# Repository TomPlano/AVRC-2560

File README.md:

# AVRC-2560
Project for interfacing Atmega2560 to the rcbus

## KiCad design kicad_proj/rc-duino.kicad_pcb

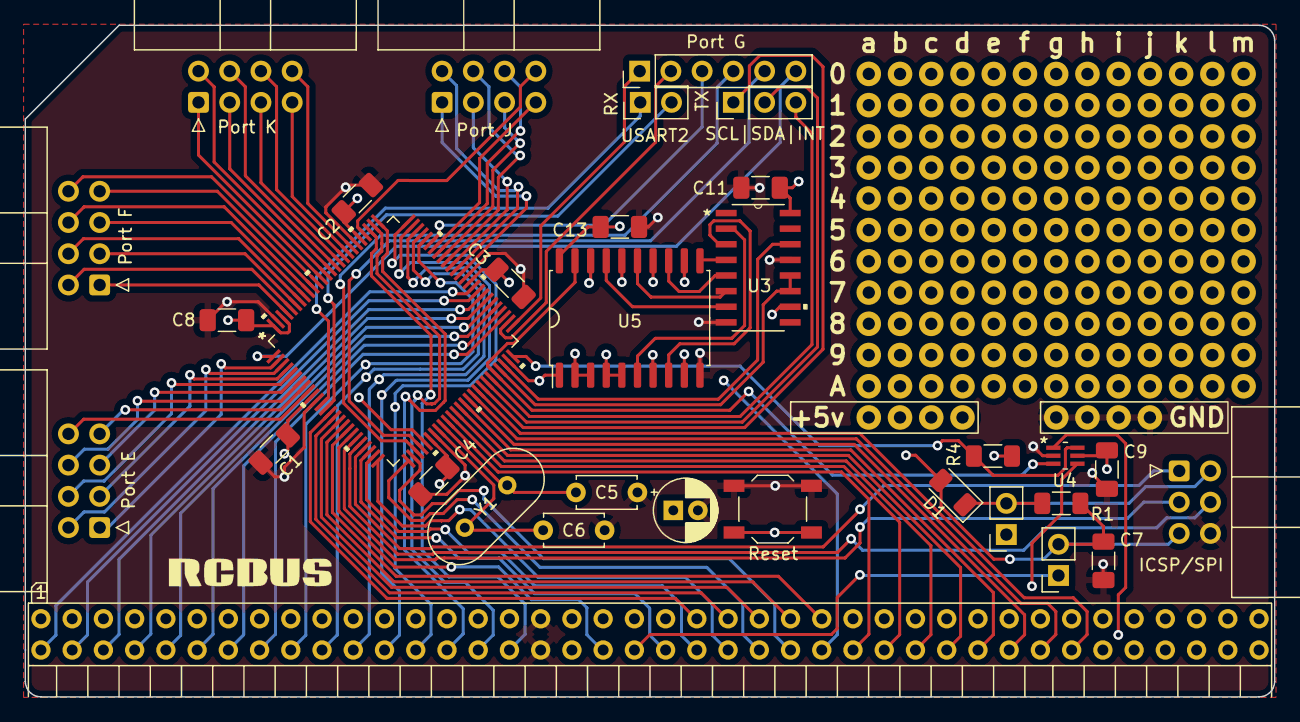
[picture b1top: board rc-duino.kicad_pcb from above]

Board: 4 copper layers, 101.6 x 54.6 mm, 35 parts (1 on the bottom side), 99 nets.

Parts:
47uf1: C_Polarized; CP_Radial_D5.0mm_P2.00mm
C1, C2, C3, C4, C8, C9, C11, C13: .1uf; C_1206_3216Metric_Pad1.33x1.80mm_HandSolder
C5, C6: 20pF; C_Disc_D4.7mm_W2.5mm_P5.00mm
C7: .1uF; C_1206_3216Metric_Pad1.33x1.80mm_HandSolder
D1: D; D_1206_3216Metric
H1: AVRC-Logo; avrc_2560
H2: RCBus Logo; RCBUS
J1: Conn_01x03_Male; PinHeader_1x03_P2.54mm_Vertical
J2: Conn_01x06_Male; PinHeader_1x06_P2.54mm_Vertical
J3: Conn_01x02_Male; PinHeader_1x02_P2.54mm_Vertical
J4, J5, J6: Conn_01x08_Male; IDC-Header_2x04_P2.54mm_Horizontal
J7: proto_area_power_gnd; protoarea
J8: Conn_02x03_Odd_Even; IDC-Header_2x03_P2.54mm_Horizontal
J10: Conn_01x04_Male; IDC-Header_2x04_P2.54mm_Horizontal
J13, J14: Conn_01x02_Male; PinSocket_1x02_P2.54mm_Vertical
R1: 10K; R_1206_3216Metric_Pad1.30x1.75mm_HandSolder
R4: 10k; R_1206_3216Metric_Pad1.30x1.75mm_HandSolder
Reset: SW_Push; SW_SPST_TL3342
U1: RCBus
U2: ATMEGA2560-16AUR
U3: 74HCT595D
U4: SN74LVC1G374DCKR
U5: 74HCT688; SOIC-20W_7.5x12.8mm_P1.27mm
Y1: 16Mhz Crystal; Crystal_HC49-U_Vertical

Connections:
/SCL: J1.1, U2.43 (PD0SCL/INT0)
/SDA: J1.2, U2.44 (PD1SDA/INT1)
/i2c int: J1.3, U2.45 (PD2RXD1/INT2)
/pe0: J6.1, U2.2 (PE0RXD0/PCINT8)
/pe1: J6.2, U2.3 (PE1TXD0)
/pe2: J6.3, U2.4 (PE2XCK0/AIN0)
/pe3: J6.4, U2.5 (PE3OC3A/AIN0)
/pe4: J6.5, U2.6 (PE4OC3B/INT4)
/pe5: J6.6, U2.7 (PE5OC3C/INT5)
/pe6: J6.7, U2.8 (PE6T3/INT6)
/pe7: J6.8, U2.9 (PE7CLKO/ICP3/INT7)
/pf0: J10.1, U2.97 (PF0ADC0)
/pf1: J10.2, U2.96 (PF1ADC1)
/pf2: J10.3, U2.95 (PF2ADC2)
/pf3: J10.4, U2.94 (PF3ADC3)
/pf4: J10.5, U2.93 (PF4ADC4/TCK)
/pf5: J10.6, U2.92 (PF5ADC5/TMS)
/pf6: J10.7, U2.91 (PF6ADC6/TDO)
/pf7: J10.8, U2.90 (PF7ADC7/TDI)
/pg0: J2.1, U2.51 (PG0*WR)
/pg1: J2.2, U2.52 (PG1*RD)
/pg2: J2.3, U2.70 (PG2ALE)
/pg3: J2.4, U2.28 (PG3TOSC2)
/pg4: J2.5, U2.29 (PG4TOSC1)
/pg5: J2.6, U2.1 (PG5OC0B)
/pj0: J4.1, U2.63 (PJ0RXD3/PCINT9)
/pj1: J4.2, U2.64 (PJ1TXD3/PCINT10)
/pj2: J4.3, U2.65 (PJ2XCK3/PCINT11)
/pj3: J4.4, U2.66 (PJ3PCINT12)
/pj4: J4.5, U2.67 (PJ4PCINT13)
/pj5: J4.6, U2.68 (PJ5PCINT14)
/pj6: J4.7, U2.69 (PJ6PCINT15)
/pj7: J4.8, U2.79 (PJ7)
/pk0: J5.1, U2.89 (PK0ADC8/PCINT16)
/pk1: J5.2, U2.88 (PK1ADC9/PCINT17)
/pk2: J5.3, U2.87 (PK2ADC10/PCINT18)
/pk3: J5.4, U2.86 (PK3ADC11/PCINT19)
/pk4: J5.5, U2.85 (PK4ADC12/PCINT20)
/pk5: J5.6, U2.84 (PK5ADC13/PCINT21)
/pk6: J5.7, U2.83 (PK6ADC14/PCINT22)
/pk7: J5.8, U2.82 (PK7ADC15/PCINT23)
/uart2_rx: J3.1, U2.12 (PH0RXD2)
/uart2_tx: J3.2, U2.13 (PH1TXD2)
A0: U1.16 (A0), U2.78 (PA0AD0), U5.2 (P0), U5.3 (R0)
A1: U1.15 (A1), U2.77 (PA1AD1), U5.4 (P1), U5.5 (R1)
A2: U1.14 (A2), U2.76 (PA2AD2), U5.7 (R2)
A3: U1.13 (A3), U2.75 (PA3AD3), U5.9 (R3)
A4: U1.12 (A4), U2.74 (PA4AD4), U5.12 (R4)
A5: U1.11 (A5), U2.73 (PA5AD5), U5.14 (R5)
A6: U1.10 (A6), U2.72 (PA6AD6), U5.16 (R6)
A7: U1.9 (A7), U2.71 (PA7AD7), U5.18 (R7)
A8: U1.8 (A8), U2.53 (PC0A8)
A9: U1.7 (A9), U2.54 (PC1A9)
Aa: U1.6 (A10), U2.55 (PC2A10)
Ab: U1.5 (A11), U2.56 (PC3A11)
Ac: U1.4 (A12), U2.57 (PC4A12)
Ad: U1.3 (A13), U2.58 (PC5A13)
Ae: U1.2 (A14), U2.59 (PC6A14)
Af: U1.1 (A15), U2.60 (PC7A15)
BusAck: U1.62 (~BUSACK), U2.14 (PH2XCK2)
BusRQ: U1.64 (~BUSRQ), U2.16 (PH4OC4B)
CLK: U1.21 (CLOCK), U2.23 (PB4OC2A/PCINT4), U4.1 (CLK)
D0: U1.27 (D0), U2.35 (PL0ICP4)
D1: U1.28 (D1), U2.36 (PL1ICP5)
D2: U1.29 (D2), U2.37 (PL2T5)
D3: U1.30 (D3), U2.38 (PL3OC5A)
D4: U1.31 (D4), U2.39 (PL4OC5B)
D5: U1.32 (D5), U2.40 (PL5OC5C)
D6: U1.33 (D6), U2.41 (PL6)
D7: U1.34 (D7), U2.42 (PL7)
Halt: U1.63 (~HALT), U2.15 (PH3OC4A)
INT: U1.22 (~INT), U2.24 (PB5OC1A/PCINT5)
M1: U1.19 (~M1), U2.19 (PB0*SS/PCINT0)
MREQ: U1.23 (~MREQ), U2.25 (PB6OC1B/PCINT6)
NMI: U1.66 (~NMI), U2.18 (PH6OC2B)
unnamed: C5.1, U2.34 (XTAL1), Y1.1
unnamed: C6.1, U2.33 (XTAL2), Y1.2
unnamed: U3.2 (Q2), U5.6 (P2)
unnamed: U3.3 (Q3), U5.8 (P3)
unnamed: U3.4 (Q4), U5.11 (P4)
unnamed: U3.5 (Q5), U5.13 (P5)
unnamed: U3.6 (Q6), U5.15 (P6)
unnamed: U3.7 (Q7), U5.17 (P7)
RD: U1.25 (~RD), U2.27 (PH7T4)
VCC: 47uf1.1, C1.1, C2.1, C3.1, C4.1, C8.2, C9.1, C11.1, C13.1, J7.1, J14.1, R4.1, U1.18 (+5V), U1.58 (+5V), U2.10 (VCC), U2.31 (VCC), U2.61 (VCC), U2.80 (VCC), U2.98 (AREF), U2.100 (AVCC), U3.10 (MR*), U3.16 (VCC), U4.5 (VCC), U5.20 (VCC)
WR: U1.24 (~WR), U2.26 (PB7OC0A/OC1C/PCINT7)
port_sr_clk: U2.47 (PD4ICP1), U3.11 (SH_CP), U3.12 (ST_CP)
port_sr_data: U2.48 (PD5XCK1), U3.14 (DS)
prog5V: D1.1 (K), J8.2, J14.2, R1.1
prog_MISO: J8.1, U2.22 (PB3MISO/PCINT3)
prog_MOSI: J8.4, U2.21 (PB2MOSI/PCINT2)
prog_gnd: 47uf1.2, C1.2, C2.2, C3.2, C4.2, C5.2, C6.2, C7.2, C8.1, C9.2, C11.2, C13.2, J7.2, J8.6, Reset.2, U1.17 (GND), U1.57 (GND), U2.11 (GND), U2.32 (GND), U2.62 (GND), U2.81 (GND), U2.99 (GND), U3.8 (GND), U3.13 (OE*), U4.2 (GND), U5.10 (GND)
prog_rst: C7.1, D1.2 (A), J8.5, J13.2, R1.2, Reset.1, U2.30 (*RESET)
prog_sck: J8.3, U2.20 (PB1SCK/PCINT1)
~IORQ: U1.26 (~IORQ), U2.49 (PD6T1), U5.1 (G)
~IO_addr_comp: R4.2, U2.50 (PD7T0), U4.6 (*OE)
~RESET: J13.1, U1.20 (~RESET)
~WAIT: U1.65 (~WAIT), U2.17 (PH5OC4C), U4.4 (Q)
~portIOrequest: U2.46 (PD3TXD1/INT3), U4.3 (D), U5.19 (P=R)

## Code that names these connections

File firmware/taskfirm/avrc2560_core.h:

#ifndef ACRV2560CORE_H
#define ACRV2560CORE_H

//cmd line for flashing a fresh board
//avrdude.exe "-CC:\Users\tompl\AppData\Local\Arduino15\packages\arduino\tools\avrdude\6.3.0-arduino17/etc/avrdude.conf" -v -V -patmega2560 -cstk500v2 -Pusb -U lfuse:w:0xff:m -U hfuse:w:0x98:m -U efuse:w:0xff:m 

#include <avr/interrupt.h>
#include <avr/io.h>

/**
 * Address Bus (J/L)
 */
#define ADDRLO_DDR DDRJ
#define ADDRLO_PORT PORTJ
#define ADDRLO_PIN PINJ

#define ADDRHI_DDR DDRL
#define ADDRHI_PORT PORTL
#define ADDRHI_PIN PINL

#define GET_ADDRLO ADDRLO_PIN
#define SET_ADDRLO(addr) ADDRLO_PORT = (addr)

#define GET_ADDRHI ADDRHI_PIN
#define SET_ADDRHI(addr) ADDRHI_PORT = (addr)

#define GET_ADDR (GET_ADDRLO | (GET_ADDRHI << 8))
#define SET_ADDR(addr) (SET_ADDRLO((addr) & 0xFF), SET_ADDRHI((addr) >> 8))

#define ADDR_INPUT (ADDRLO_DDR = 0x00, ADDRHI_DDR = 0x00)
#define ADDR_OUTPUT (ADDRLO_DDR = 0xFF, ADDRHI_DDR = 0xFF)
#define ADDR_TSTATE  (ADDR_INPUT, ADDRLO_PORT=0x00,ADDRHI_PORT=0x00)
/**
 * Data Bus (K)
 */
#define DATA_DDR DDRK
#define DATA_PORT PORTK
#define DATA_PIN PINK

#define DATA_INPUT DATA_DDR = 0x00
#define DATA_OUTPUT DATA_DDR = 0xFF
#define DATA_TSTATE (DATA_INPUT, DATA_PORT = 0x00)

#define GET_DATA DATA_PIN
#define SET_DATA(data) DATA_PORT = (data)

/**
 * Port B Map
 */

#define M1 (1 << PINB0)
#define SPI_CLK (1 << PINB1)
#define SPI_MOSI (1 << PINB2)
#define SPI_MISO (1 << PINB3)
#define MREQ (1 << PINB4)
#define WR (1 << PINB5)
#define RD (1 << PINB6)
#define CLK (1 << PINB7)

/**
 * Port B Manipulation
 */

#define GET_M1 (PINB & M1)
#define GET_MREQ (PINB & MREQ)
#define GET_WR (PINB & WR)
#define GET_RD (PINB & RD)
#define GET_CLK (PINB & CLK)

/**
 * Port D Map
 */
#define I2C_SCL  (1 << PIND0)
#define I2C_SDA (1 << PIND1)
#define I2C_INT (1 << PIND2)
#define PORT_IO_REQUEST (1 << PIND3)
#define INT (1 << PIND4)
#define NMI (1 << PIND5)
#define IORQ (1 << PIND6)
#define IO_ADDR_COMP (1 << PIND7)

/**
 * Port D Manipulation
 */
#define GET_PORT_IO_REQUEST (PIND & PORT_IO_REQUEST)
#define GET_INT (PIND & INT)
#define GET_NMI (PIND & NMI)
#define GET_IORQ (PIND & IORQ)

#define IO_ADDR_COMP_HI PIND |= IO_ADDR_COMP
#define IO_ADDR_COMP_LO PIND &= ~IO_ADDR_COMP

/**
 * Port G Map
 */
#define MAN_CLK_EN (1 << PING4)
#define MAN_CLK_TOG (1 << PING5)

#define MAN_CLK_EN_HI PORTG |= MAN_CLK_EN
#define MAN_CLK_EN_LO PORTG &= ~MAN_CLK_EN

#define MAN_CLK_TOG_HI PORTG |= MAN_CLK_TOG
#define MAN_CLK_TOG_LO PORTG &= ~MAN_CLK_TOG

/**
 * Port H Map
 */
#define UART2_RX  (1 << PINH0)
#define UART2_TX (1 << PINH1)
#define HALT (1 << PINH2)
#define PORT_SR_DATA (1 << PINH3)
#define PORT_SR_CLK (1 << PINH4)
#define BUSACK (1 << PINH5)
#define BUSRQ (1 << PINH6)
#define WAIT (1 << PINH7)


/**
 * Port H Manipulation
 */

#define GET_HALT (PINH & HALT)
#define GET_BUSACK (PINH & BUSACK)
#define GET_BUSRQ (PINH & BUSRQ)
#define GET_WAIT  (PINH & WAIT)

#define PORT_SR_DATA_HI PORTH |= PORT_SR_DATA
#define PORT_SR_DATA_LO PORTH &= ~PORT_SR_DATA

#define PORT_SR_CLK_HI PORTH |= PORT_SR_CLK
#define PORT_SR_CLK_LO PORTH &= ~PORT_SR_CLK
#define PORT_SR_CLK_TOG (PORT_SR_CLK_HI, PORT_SR_CLK_LO)


#define BUSRQ_HI PORTH |= BUSRQ
#define BUSRQ_LO PORTH &= ~BUSRQ

/**
 * DDR defaults
 */
// CLK,Rd,WR,MRQ,prog_miso,prog_mosi,prog_sck,m1
#define DDRB_DEFAULT 0x00
//PD = ~IO_addr_comp, ~IORQ, NMI, INT, ~portIOReq, ~i2c int,SDA,SCL
#define DDRD_DEFAULT 0b10000011
//~WAIT,BusRQ,BusAck,port_sr_clk,port_sr_data,Halt,uart2_tx,uart2_rx
#define DDRH_DEFAULT 0b00011011
//X,X,man_clock_toggle,man_clock_en,pg3,pg2,pg1,pg0
#define DDRG_DEFAULT 0b00110000


//ISR related global data 
volatile byte direction = 0;
volatile byte indata = 0; //data recived from host
volatile byte outData = 0; // data staged from sending to host 
volatile byte err = 0;
volatile bool hostIOOccured = false;

ISR(INT3_vect) {
  /*
  Init State:
  shift register Q0-7 contain the address that the avr will listen on, set at boot
  ~{PortIOREquest} pulled up by mcu internal resistor
  ~{IO_add_comp} is held low, flip flop passing ioreq out to wait
  A0-7 + ~{IORQ} are non-matching

  IO sequence:
  1. cpu brings iorq rd/wt low with matching port address on bus
  2. portIOrequest goes low after matching addr[2:7] with sr[2:7]  and gets latched onto waitline with next clk pulse
  2.5 avr falling edge intterrupt trigger on portIOrequest
  3. avr checks RD and WR lines to determine what request is being made

  Timing Notes:
  Single 8bit Read, from iorq going low to wait and busreq release : between 8 and 9 us (58 to 66 clock cycles, 15 to 17 machine cycles )
  Single 8bit Write, from iorq going low to wait release : between 8 and 6.5 us (44 to 48 clock cycles, 11 to 12 machine cycles)

  will need to retime after next revision and removal of hash/unhash functions

  */

  //report IO to rest of AVR
  hostIOOccured = true;


  //read ~WR and ~RD pins
  err = 0;
  byte _WRPin = GET_WR;
  byte _RDPin = GET_RD;

  if (_WRPin != WR && _RDPin == RD) {
    /*
      if write:
        1. avr data pins default to input/high Z and collects value
        2. avr tristate decoding logic by brining ~{IO_add_comp} low, wait goes high from pullup on cpu card, latch is set high on next clk pluse
      */
    //read data bus
    indata = GET_DATA;
    // inline asm to make to compiler and timing behave
    asm("sbi %0, %1 \n"
        "nop\n"
        "nop\n"
        "nop\n"
        "nop\n"
        "nop\n"
        "nop\n"
        "nop\n"
        "nop\n"
        "nop\n"
        "cbi %0, %1 \n"
        :
        : "I"(_SFR_IO_ADDR(PORTD)), "I"(PORTD7));
    return;
  } else if (_RDPin != RD && _WRPin == WR) {
    /*
      if read:
        4. avr sets databus to output , and output low, then  sets value
        5. avr then asserts the busreq line to essentially stall the cpu in tristate after the databus has been read
        6. avr tristate decoding logic by brining ~{IO_add_comp} high , wait goes high from pullup on cpu card, latch is set high on next clk pluse
        7. cpu reads data lines now that wait is clear
        8. cpu sees asserted bus req at begining of last m cycle of read
        9. cpu tristates its pins
        10. avr Poll on busack, proceed after it goes low
        11. avr tristate the databus
        12. avr reenable address decoding by brining ~{IO_add_comp} low
        13. avr release busreq
      */
    //set data lines to output
    DATA_OUTPUT;
    //clear databus
    SET_DATA(0x00);
    //output true data
    SET_DATA(outData);
    //set busreq to output
    DDRH = DDRH | BUSRQ;

    //assert bus req low
    BUSRQ_LO;
    //avr tristate decoding logic by brining ~{IO_add_comp} high
    asm("sbi %0, %1 \n"
        :
        : "I"(_SFR_IO_ADDR(PORTD)), "I"(PORTD7));
    // wait for cpu to read data, this will be indicated by bus ack going low on pinh5, use avrlibc/io for stibility
    loop_until_bit_is_clear(PINH, 5);

    //trisatate data bus
    DATA_TSTATE;
    // reanable addr decode
    asm("cbi %0, %1 \n"
        :
        : "I"(_SFR_IO_ADDR(PORTD)), "I"(PORTD7));
    // release busreq and set to high Z
    PORTH = PORTH | BUSRQ;
    //set busreq to input
    DDRH = DDRH & ~BUSRQ;
  } else {
    err = 1;
  }
}

void ioaddrSet(byte addr) {
  byte i;
  for (i = 0; i < 8; i++) {
    PORT_SR_DATA_LO;
    PORT_SR_CLK_TOG;
  }
  for (i = 0; i < 8; i++) {
    //digitalWrite(SRDATA, (addr & 128) != 0);
    ((addr & 128) != 0) ? PORT_SR_DATA_HI : PORT_SR_DATA_LO;
    addr <<= 1;
    PORT_SR_CLK_TOG;
  }
  PORT_SR_CLK_TOG;
}

void initRCBus(){
  DATA_TSTATE;
  ADDR_TSTATE;
  DDRB = DDRB_DEFAULT;
  DDRD = DDRD_DEFAULT;
  DDRH = DDRH_DEFAULT;
  DDRG = DDRG_DEFAULT;
  ioaddrSet(0b11001000);  //203
}

void enableRCbusinterrupt(){
    //set up port IO interrup ctrl,
  EIMSK = 0b00000000;          //disable INT3&INT2 before setting its mode
  EICRA = 0b10100000;          //INT3&INT2 triggers on FALLING EDGE
  EIMSK = 0b00001100;          //enable INT3
  IO_ADDR_COMP_LO;  //force ~IO_addr_comp (pd7) low, enabling wait latching
}

void initUserPorts(){
  //set unused user ports to output
  //DDRA = 0xFF;
  DDRC = 0xFF;
  DDRE = 0xFF;
  DDRF = 0xFF;
  DDRG = DDRG | 0b00001111;
  PORTA = 0xFF;
  PORTC = 0xFF;
  PORTE = 0xFF;
  PORTF = 0xFF;
  PORTG = PORTG | 0b00001111;
}

#endif /*ACRV2560CORE_H*/

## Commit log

2024-01-12 first push for public review
2024-01-18 got encoders working as external dev
2024-01-22 revising code into multitasking freeRTOS implementation
2024-02-17 checking in before major relayout of ctrl board
2024-09-04 major rework
2024-09-25 moving to a custom interput software system
2024-10-31 checkout before reimage

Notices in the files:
parts and their libraries:
Copyright 2021 Accelerated Designs. All rights reserved.
